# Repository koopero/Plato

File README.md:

# Project Plato

The goal is the creation of a full set of all 5 regular polyhedra, or Platonic Solids, using programmable LEDs and 3D printed plastic.

- Open-source hardware & software.
- AI-assisted programming and design practices.
- Iteratative & improvisational design processes.
- Parametric practical geometry. 
- PCB design using Kicad

# Subprojects

|Project|Description|Status|
|---|---|---|
|[Plato_A2](Plato_A2/README.md)|Triangular LED board|Awaiting manufacture|
|[Plato_A1](Plato_A1/README.md)|Triangular LED board|Failed testing|
|[Plato_B1](Plato_B1/README.md)|ESP32 control board|In-progress|
|[Plato_C1](Plato_C1/README.md)|Tetrahedron casing for Plato_A1|Success|

# Tooling

- Kicad
- Python
- ImageMagick
- OpenSCAD
- Blender

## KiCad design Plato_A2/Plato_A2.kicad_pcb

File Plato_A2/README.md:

# Plato_A2

*Please note that this design has failed testing and should not be used.*

`Plato_A2` is a regular triangle, made of light and plastic, with a dimension of about an inch. This subassembly is meant as an experiment in:

|Spec|Value|Unit|
|----|-----|----|
|LED Count| 28 | WS2812B 2020|

# Process

- Iterate design scripts from `Plato_A1` ( `Plato_A2_design.py` and `kicad_align_leds.py` )
  - Better LED orientation.
  - Export of holes and jumpers.
  - Placement of capacitors.
- Start a new project in Kicad
- Create schematic with all parts.
- Switch to PCB designer and import generated file `Plato_A2_board.dxf` into edge cut layer.
- Copy and paste the script `kicad_align_leds.py` into Kicad's scripting console to position LEDs.
- Manually place bulk capacitors and resistor.
- Draw routes to connect all components, using vias beneath LEDs.
- Create wicked silkscreen for front.
  - Create `art/Plato_A2_Art.png` in Gimp
  - Import png to Inkscape
  - *Trace Bitmap* with *Color Quantization*
  - *Path / Break Apart*
  - Delete image and background shape
  - Export to `art/Plato_A2_Art.dxf`
  - Import to kicad silkscreen layer.
  - Manually delete overlaps after DRC.
- Run DRC and fix problems.
- Use Kicad's Fabrication Toolkit plugin to aid in preparing the board for fabrication.
- Use [JLCPCB](https://jlcpcb.com/)'s online tools to order 5 copies of the board.

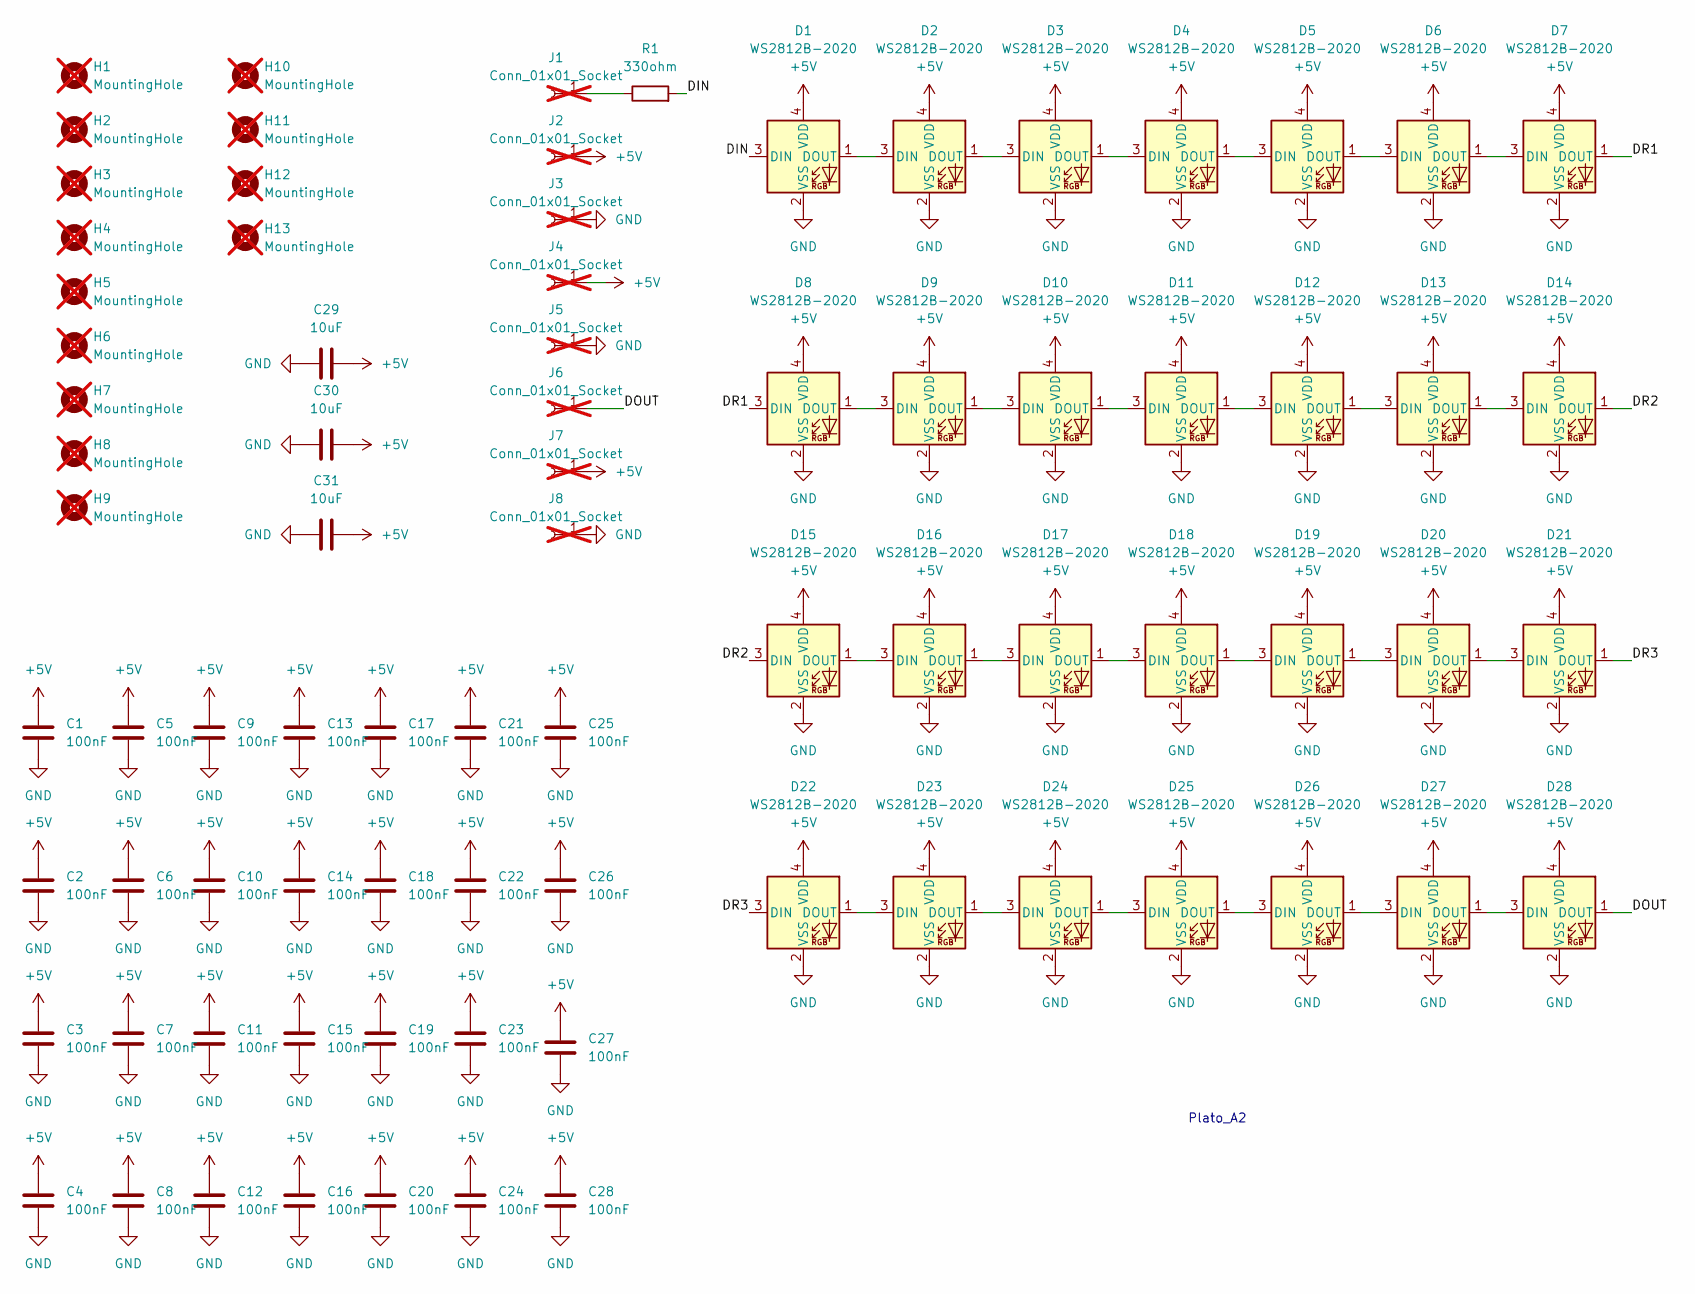
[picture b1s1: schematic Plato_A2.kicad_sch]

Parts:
C1, C2, C3, C4, C5, C6, C7, C8, C9, C10, C11, C12, C13, C14, C15, C16, C17, C18, C19, C20, C21, C22, C23, C24, C25, C26, C27, C28: 100nF; C_0402_1005Metric; LCSC C1525
C29, C30, C31: 10uF; C_0603_1608Metric; LCSC C96446
D1, D2, D3, D4, D5, D6, D7, D8, D9, D10, D11, D12, D13, D14, D15, D16, D17, D18, D19, D20, D21, D22, D23, D24, D25, D26, D27, D28: WS2812B-2020; Plato_WS2812B-2020; LCSC C965555
H1, H2, H3, H4, H5, H6, H7, H8, H9, H10, H11, H12, H13: MountingHole; MountingHoleM1; not fitted
J1, J6: Conn_01x01_Socket; DataHole; not fitted
J2, J3, J4, J5, J7, J8: Conn_01x01_Socket; PowerHole; not fitted
R1: 330ohm; R_0402_1005Metric; LCSC C25104

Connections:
+5V: C1.1, C2.1, C3.1, C4.1, C5.1, C6.1, C7.1, C8.1, C9.1, C10.1, C11.1, C12.1, C13.1, C14.1, C15.1, C16.1, C17.1, C18.1, C19.1, C20.1, C21.1, C22.1, C23.1, C24.1, C25.1, C26.1, C27.1, C28.1, C29.2, C30.2, C31.2, D1.4 (VDD), D2.4 (VDD), D3.4 (VDD), D4.4 (VDD), D5.4 (VDD), D6.4 (VDD), D7.4 (VDD), D8.4 (VDD), D9.4 (VDD), D10.4 (VDD), D11.4 (VDD), D12.4 (VDD), D13.4 (VDD), D14.4 (VDD), D15.4 (VDD), D16.4 (VDD), D17.4 (VDD), D18.4 (VDD), D19.4 (VDD), D20.4 (VDD), D21.4 (VDD), D22.4 (VDD), D23.4 (VDD), D24.4 (VDD), D25.4 (VDD), D26.4 (VDD), D27.4 (VDD), D28.4 (VDD), J2.1, J4.1, J7.1
/DIN: D1.3 (DIN), R1.2
/DOUT: D28.1 (DOUT), J6.1
/DR1: D7.1 (DOUT), D8.3 (DIN)
/DR2: D14.1 (DOUT), D15.3 (DIN)
/DR3: D21.1 (DOUT), D22.3 (DIN)
GND: C1.2, C2.2, C3.2, C4.2, C5.2, C6.2, C7.2, C8.2, C9.2, C10.2, C11.2, C12.2, C13.2, C14.2, C15.2, C16.2, C17.2, C18.2, C19.2, C20.2, C21.2, C22.2, C23.2, C24.2, C25.2, C26.2, C27.2, C28.2, C29.1, C30.1, C31.1, D1.2 (VSS), D2.2 (VSS), D3.2 (VSS), D4.2 (VSS), D5.2 (VSS), D6.2 (VSS), D7.2 (VSS), D8.2 (VSS), D9.2 (VSS), D10.2 (VSS), D11.2 (VSS), D12.2 (VSS), D13.2 (VSS), D14.2 (VSS), D15.2 (VSS), D16.2 (VSS), D17.2 (VSS), D18.2 (VSS), D19.2 (VSS), D20.2 (VSS), D21.2 (VSS), D22.2 (VSS), D23.2 (VSS), D24.2 (VSS), D25.2 (VSS), D26.2 (VSS), D27.2 (VSS), D28.2 (VSS), J3.1, J5.1, J8.1
unnamed: D1.1 (DOUT), D2.3 (DIN)
unnamed: D2.1 (DOUT), D3.3 (DIN)
unnamed: D3.1 (DOUT), D4.3 (DIN)
unnamed: D4.1 (DOUT), D5.3 (DIN)
unnamed: D5.1 (DOUT), D6.3 (DIN)
unnamed: D6.1 (DOUT), D7.3 (DIN)
unnamed: D8.1 (DOUT), D9.3 (DIN)
unnamed: D9.1 (DOUT), D10.3 (DIN)
unnamed: D10.1 (DOUT), D11.3 (DIN)
unnamed: D11.1 (DOUT), D12.3 (DIN)
unnamed: D12.1 (DOUT), D13.3 (DIN)
unnamed: D13.1 (DOUT), D14.3 (DIN)
unnamed: D15.1 (DOUT), D16.3 (DIN)
unnamed: D16.1 (DOUT), D17.3 (DIN)
unnamed: D17.1 (DOUT), D18.3 (DIN)
unnamed: D18.1 (DOUT), D19.3 (DIN)
unnamed: D19.1 (DOUT), D20.3 (DIN)
unnamed: D20.1 (DOUT), D21.3 (DIN)
unnamed: D22.1 (DOUT), D23.3 (DIN)
unnamed: D23.1 (DOUT), D24.3 (DIN)
unnamed: D24.1 (DOUT), D25.3 (DIN)
unnamed: D25.1 (DOUT), D26.3 (DIN)
unnamed: D26.1 (DOUT), D27.3 (DIN)
unnamed: D27.1 (DOUT), D28.3 (DIN)
unnamed: J1.1, R1.1

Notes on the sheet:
Plato_A2

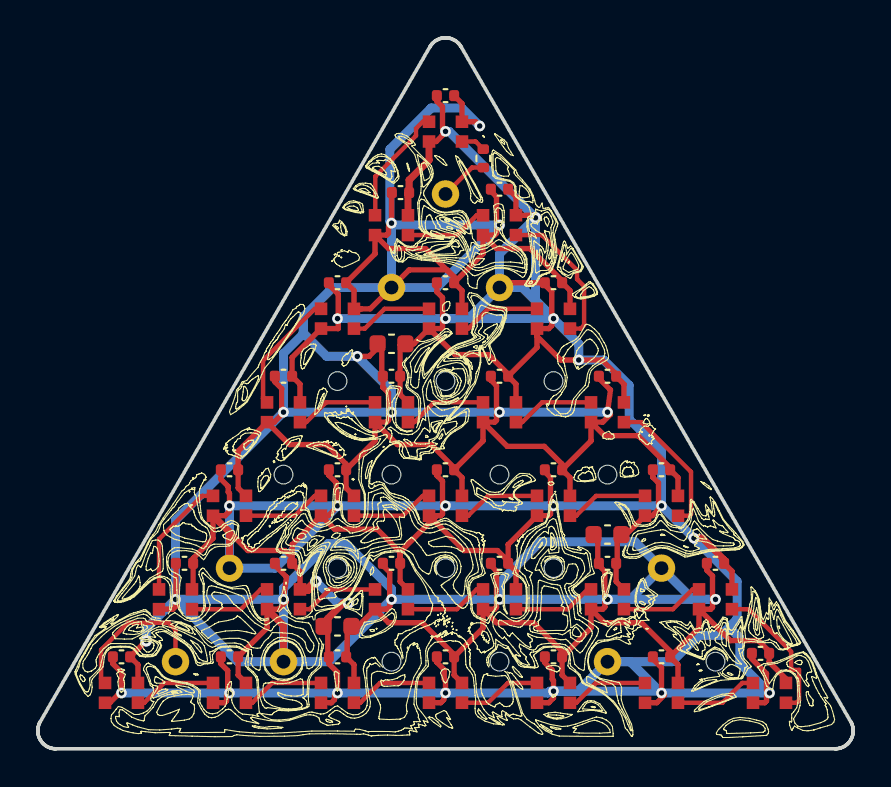
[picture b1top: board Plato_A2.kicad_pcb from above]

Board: 2 copper layers, 45.3 x 39.5 mm, 81 parts (0 on the bottom side), 32 nets.

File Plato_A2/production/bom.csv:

Designator,Footprint,Quantity,Value,LCSC Part #
"C1, C10, C11, C12, C13, C14, C15, C16, C17, C18, C19, C2, C20, C21, C22, C23, C24, C25, C26, C27, C28, C3, C4, C5, C6, C7, C8, C9",0402,28,100nF,C1525
"C29, C30, C31",0603,3,10uF,C96446
"D1, D10, D11, D12, D13, D14, D15, D16, D17, D18, D19, D2, D20, D21, D22, D23, D24, D25, D26, D27, D28, D3, D4, D5, D6, D7, D8, D9",Plato_WS2812B-2020,28,WS2812B-2020,C965555
R1,0402,1,330ohm,C25104

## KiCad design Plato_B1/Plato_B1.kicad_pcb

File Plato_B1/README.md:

# Features

- ESP32-WROOM-32 Dual Core
- 

*After years of stringing together ESP32 Devkits, on breadboards and in boxes, I have decided to build.**

- MPU6050 accelerometer & gyro with independant i2c bus. 
- MicroUSB programming port (no charging).
- 4x exposed GPIO pins, each with accompanying 5V, and GND.
- 4x WS2812B 2020 LEDs, acting as both status display and signal booster. 
- 4x LED pin sets, with power from 5V or VBAT.
- Beefy 2A 5V buck converter, intended to run from 2S+ battery.
- Connection for external power switch.
- 6 pin auxillary connector with power & i2c.

At the end of the board

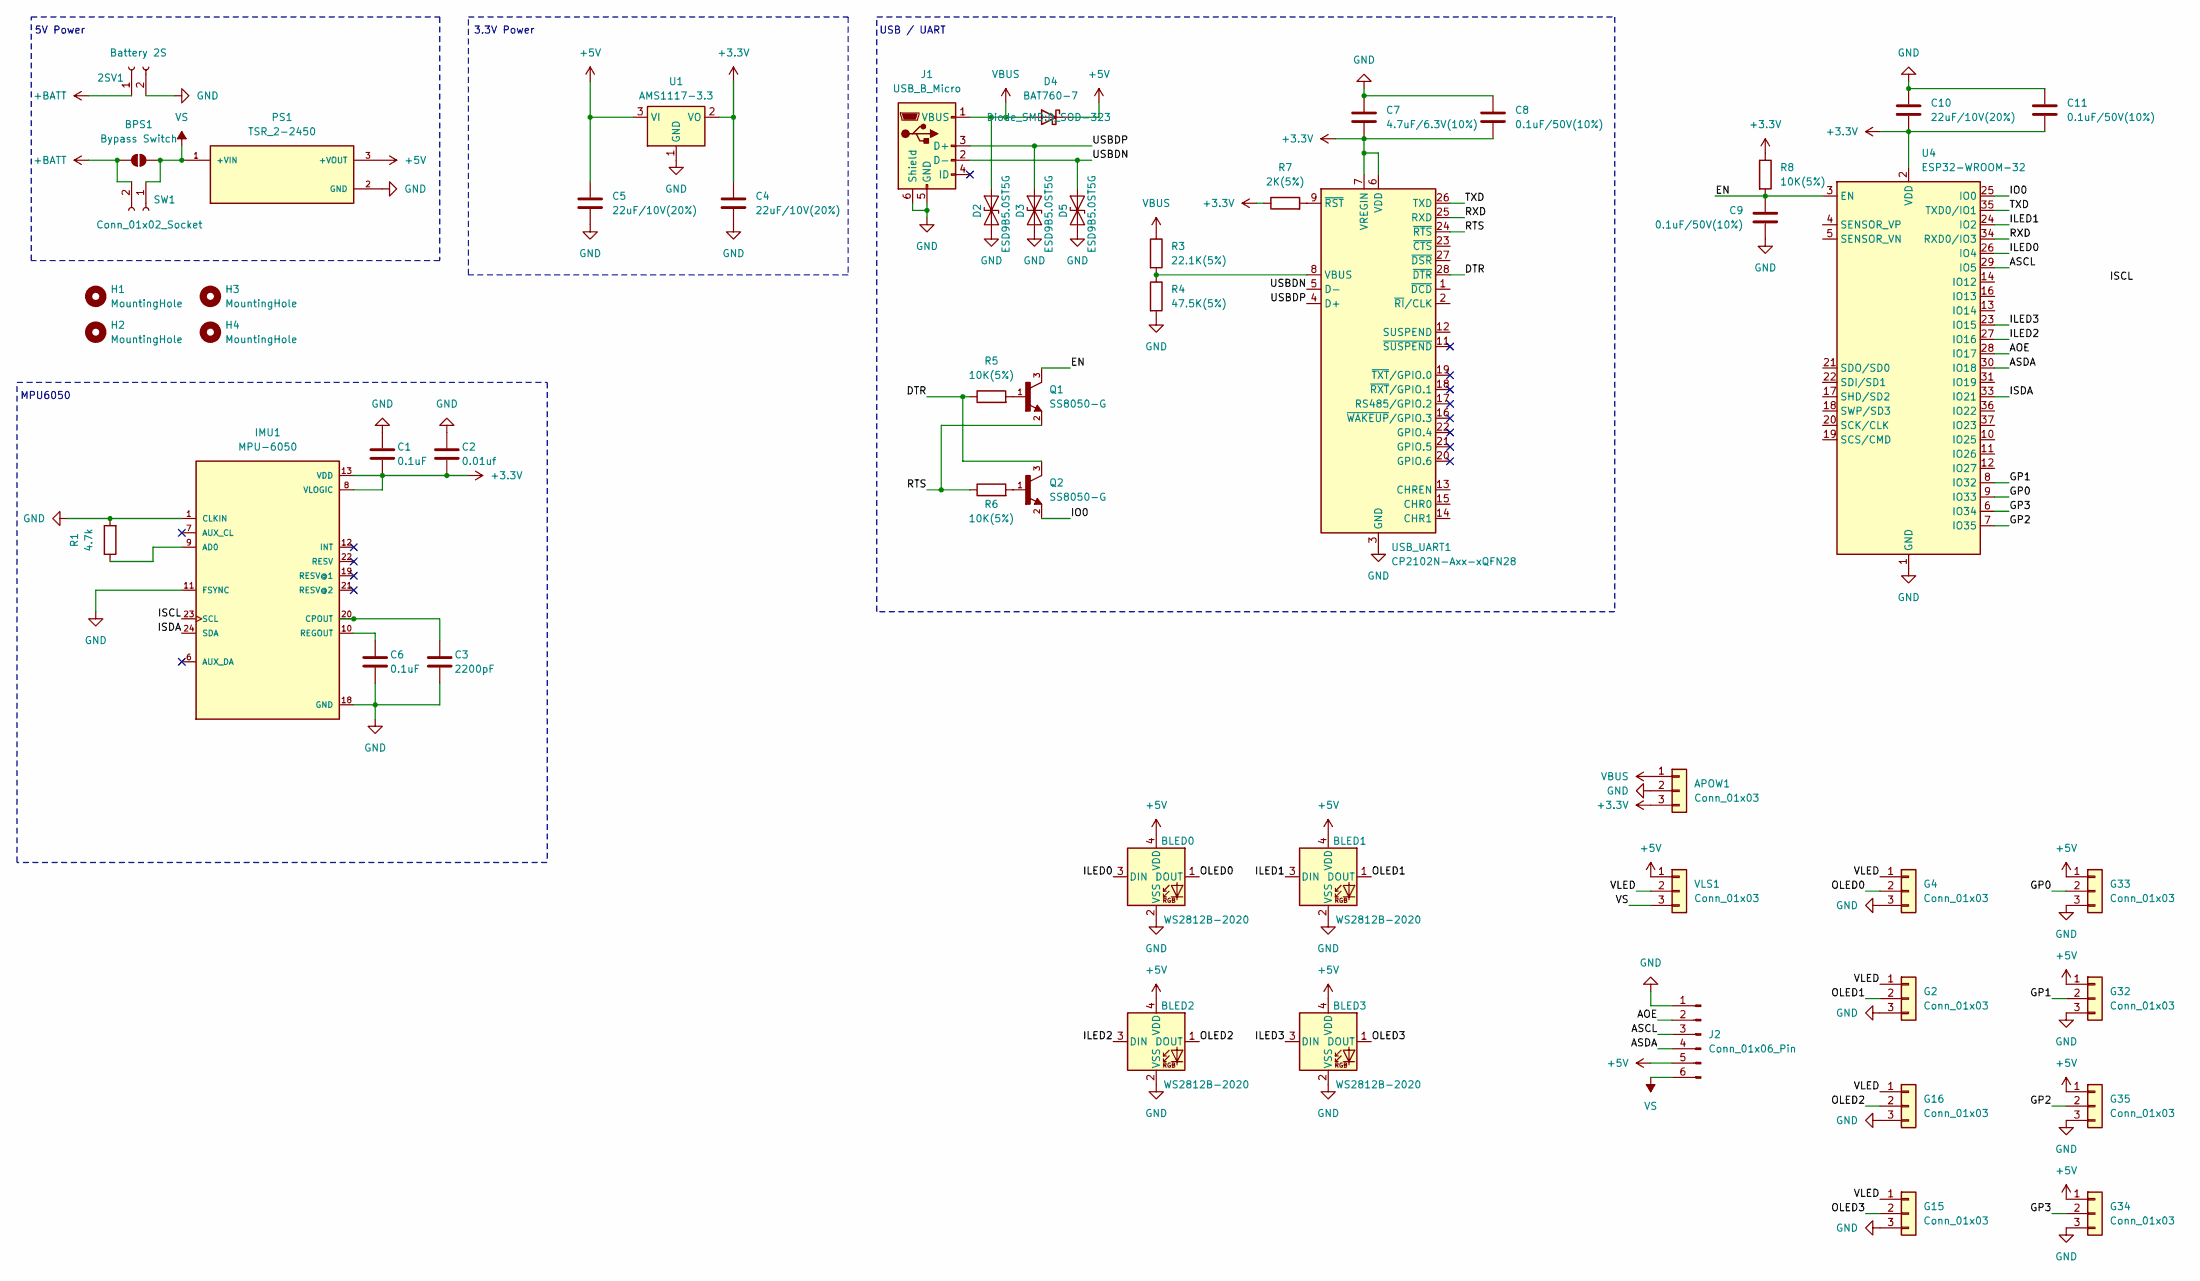
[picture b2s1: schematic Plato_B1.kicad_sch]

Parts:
2SV1: Battery 2S; PinHeader_1x02_P2.54mm_Vertical
APOW1: Conn_01x03; PinHeader_1x03_P2.54mm_Vertical
BLED0, BLED1, BLED2, BLED3: WS2812B-2020; LED_WS2812B-2020_PLCC4_2.0x2.0mm
BPS1: Bypass Switch; SolderJumper-2_P1.3mm_Open_TrianglePad1.0x1.5mm
C1, C6: 0.1uF; C_0603_1608Metric
C2: 0.01uf; C_0603_1608Metric
C3: 2200pF; LED_1210_3225Metric
C4, C5, C10: 22uF/10V(20%); C_1206_3216Metric
C7: 4.7uF/6.3V(10%); C_1206_3216Metric
C8, C9, C11: 0.1uF/50V(10%); C_0603_1608Metric
D2, D3, D5: ESD9B5.0ST5G; D_SOD-323
D4: BAT760-7; D_SOD-323
G2, G4, G15, G16, G32, G33, G34, G35: Conn_01x03; Centred_Pin1x3_2.54mm
H1, H2, H3, H4: MountingHole; MountingHole_2.2mm_M2
IMU1: MPU-6050; QFN50P400X400X95-24N; PARTREV 3.4
J1: USB_B_Micro; USB_Micro-B_Amphenol_10103594-0001LF_Horizontal
J2: Conn_01x06_Pin; PinHeader_1x06_P2.54mm_Vertical
PS1: TSR_2-2450; CONV_TSR_2-2450; PARTREV May 14, 2020
Q1, Q2: SS8050-G; SOT-23; PARTREV A
R1: 4.7k; R_0603_1608Metric
R3: 22.1K(5%); R_0603_1608Metric
R4: 47.5K(5%); R_0603_1608Metric
R5, R6, R8: 10K(5%); R_0603_1608Metric
R7: 2K(5%); R_0603_1608Metric
SW1: Conn_01x02_Socket; PinHeader_1x02_P2.54mm_Vertical
U1: AMS1117-3.3; SOT-223-3_TabPin2
U4: ESP32-WROOM-32
USB_UART1: CP2102N-Axx-xQFN28; QFN-28-1EP_5x5mm_P0.5mm_EP3.35x3.35mm
VLS1: Conn_01x03; PinHeader_1x03_P2.54mm_Vertical

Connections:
+3.3V: APOW1.3, C1.2, C2.2, C4.1, C7.2, C8.2, C10.2, C11.2, IMU1.8 (VLOGIC), IMU1.13 (VDD), R7.1, R8.1, U1.2 (VO), U4.2 (VDD), USB_UART1.6 (VDD), USB_UART1.7 (VREGIN)
+5V: BLED0.4 (VDD), BLED1.4 (VDD), BLED2.4 (VDD), BLED3.4 (VDD), C5.1, D4.1 (K), G32.1, G33.1, G34.1, G35.1, J2.5, PS1.3 (+VOUT), U1.3 (VI), VLS1.1
+BATT: 2SV1.1, BPS1.1 (A), SW1.2
/AOE: J2.2, U4.28 (IO17)
/ASCL: J2.3, U4.29 (IO5)
/ASDA: J2.4, U4.30 (IO18)
/DTR: Q2.3, R5.1, USB_UART1.28 (~DTR)
/EN: C9.1, Q1.3, R8.2, U4.3 (EN)
/GP0: G33.2, U4.9 (IO33)
/GP1: G32.2, U4.8 (IO32)
/GP2: G35.2, U4.7 (IO35)
/GP3: G34.2, U4.6 (IO34)
/ILED0: BLED0.3 (DIN), U4.26 (IO4)
/ILED1: BLED1.3 (DIN), U4.24 (IO2)
/ILED2: BLED2.3 (DIN), U4.27 (IO16)
/ILED3: BLED3.3 (DIN), U4.23 (IO15)
/IO0: Q2.2, U4.25 (IO0)
/ISCL: IMU1.23 (SCL)
/ISDA: IMU1.24 (SDA), U4.33 (IO21)
/OLED0: BLED0.1 (DOUT), G4.2
/OLED1: BLED1.1 (DOUT), G2.2
/OLED2: BLED2.1 (DOUT), G16.2
/OLED3: BLED3.1 (DOUT), G15.2
/RTS: Q1.2, R6.1, USB_UART1.24 (~RTS)
/RXD: U4.34 (RXD0/IO3), USB_UART1.25 (RXD)
/TXD: U4.35 (TXD0/IO1), USB_UART1.26 (TXD)
/USBDN: D5.2 (A2), J1.2 (D-), USB_UART1.5 (D-)
/USBDP: D3.2 (A2), J1.3 (D+), USB_UART1.4 (D+)
/VLED: G2.1, G4.1, G15.1, G16.1, VLS1.2
GND: 2SV1.2, APOW1.2, BLED0.2 (VSS), BLED1.2 (VSS), BLED2.2 (VSS), BLED3.2 (VSS), C1.1, C2.1, C3.2, C4.2, C5.2, C6.2, C7.1, C8.1, C9.2, C10.1, C11.1, D2.1 (A1), D3.1 (A1), D5.1 (A1), G2.3, G4.3, G15.3, G16.3, G32.3, G33.3, G34.3, G35.3, IMU1.1 (CLKIN), IMU1.11 (FSYNC), IMU1.18 (GND), J1.5 (GND), J1.6 (Shield), J2.1, PS1.2 (GND), R1.2, R4.2, U1.1 (GND), U4.1 (GND), U4.15 (GND), U4.38 (GND), U4.39 (GND), USB_UART1.3 (GND), USB_UART1.29 (GND)
unnamed: IMU1.9 (AD0), R1.1
unnamed: C3.1, IMU1.20 (CPOUT)
unnamed: C6.1, IMU1.10 (REGOUT)
unnamed: Q1.1, R5.2
unnamed: Q2.1, R6.2
unnamed: R3.2, R4.1, USB_UART1.8 (VBUS)
unnamed: R7.2, USB_UART1.9 (~RST)
VBUS: APOW1.1, D2.2 (A2), D4.2 (A), J1.1 (VBUS), R3.1
VS: BPS1.2 (B), J2.6, PS1.1 (+VIN), SW1.1, VLS1.3

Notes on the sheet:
USB / UART
5V Power
MPU6050
3.3V Power

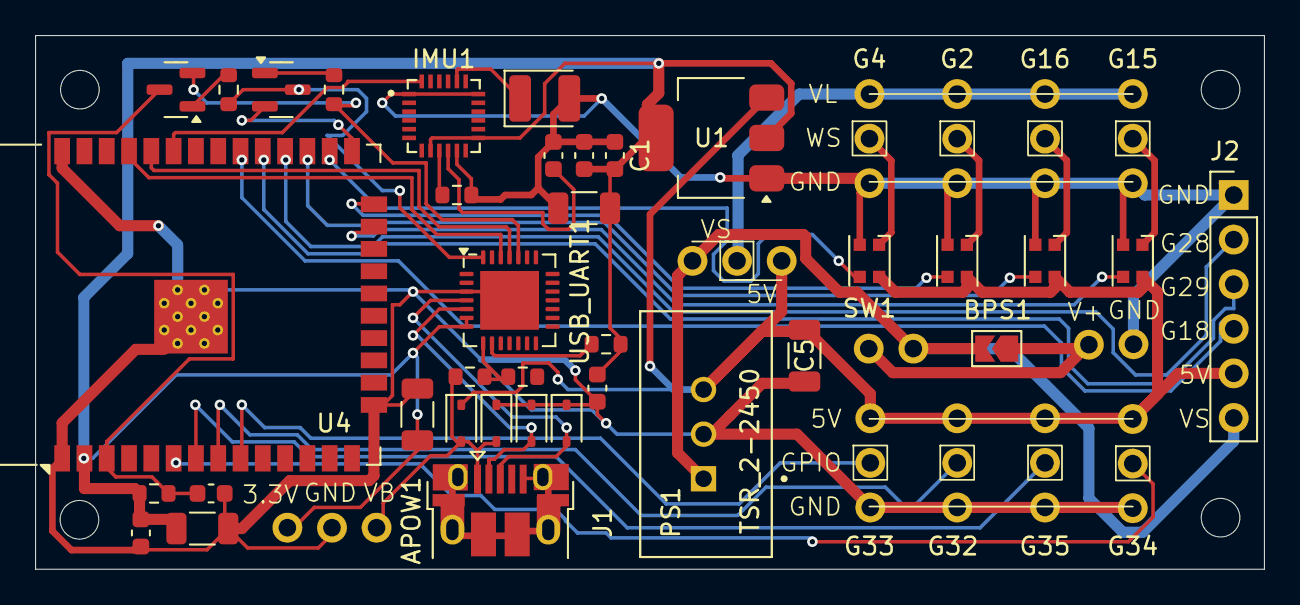
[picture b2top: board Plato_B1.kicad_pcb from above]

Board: 2 copper layers, 70.0 x 30.4 mm, 52 parts (0 on the bottom side), 38 nets.

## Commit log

2024-04-25 Plato_A1 initial
2024-04-29 Before ripping up Plato_A1
2024-05-02 Plato_B1 initial
2024-05-02 Plato_A2 initial
2024-05-02 Plato_C1 initial test
2024-05-02 Abortative redesign
2024-05-02 Restore final product
2024-05-02 Update design and output
2024-05-02 Update docs
